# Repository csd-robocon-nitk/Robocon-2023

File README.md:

# Overview
This repository contains all the codes and PCB designs used for ABU Robocon 2023.

# Technolgies Used

# Directory Structure

- ```Experimental``` Contains all the arduino codes used during the ideation and prototyping phase. The folder also contains python codes used for image processing using Kinect cameras.

- ```Final Codes``` Contains all the arduino codes used in the competition.

- ```PCB``` Designs of the PCBs used in the robots is present here.

- ```Media``` Folder for keeping images for documentation.

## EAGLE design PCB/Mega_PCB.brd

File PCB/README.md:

# PCB designs for the Mega and Nano PCB for Robocon 2023

The elephant and the rabbit robot each uses two PCBs. The PCBs have been designed in Autodesk Eagle.

## Mega PCB

*Mega PCB*

The first PCB contains the Arduino Mega (Also compatible with Arduino Giga, and Arduino Due). This PCB is connected to all the motors responsible for the navigation of the robots and IMU module. The PCB also has pin headers for ESP-07 for WiFi communication.

## Nano PCB

*Nano PCB*

The second PCB contains the Arduino Nano (Also compatible with boards of same form factor as Arduino Nano). This PCB controls the rest of the robot, which includes the shooting and picking mechanism. 

The boards have been designed such that they can be used together or as seperate standalone modules.

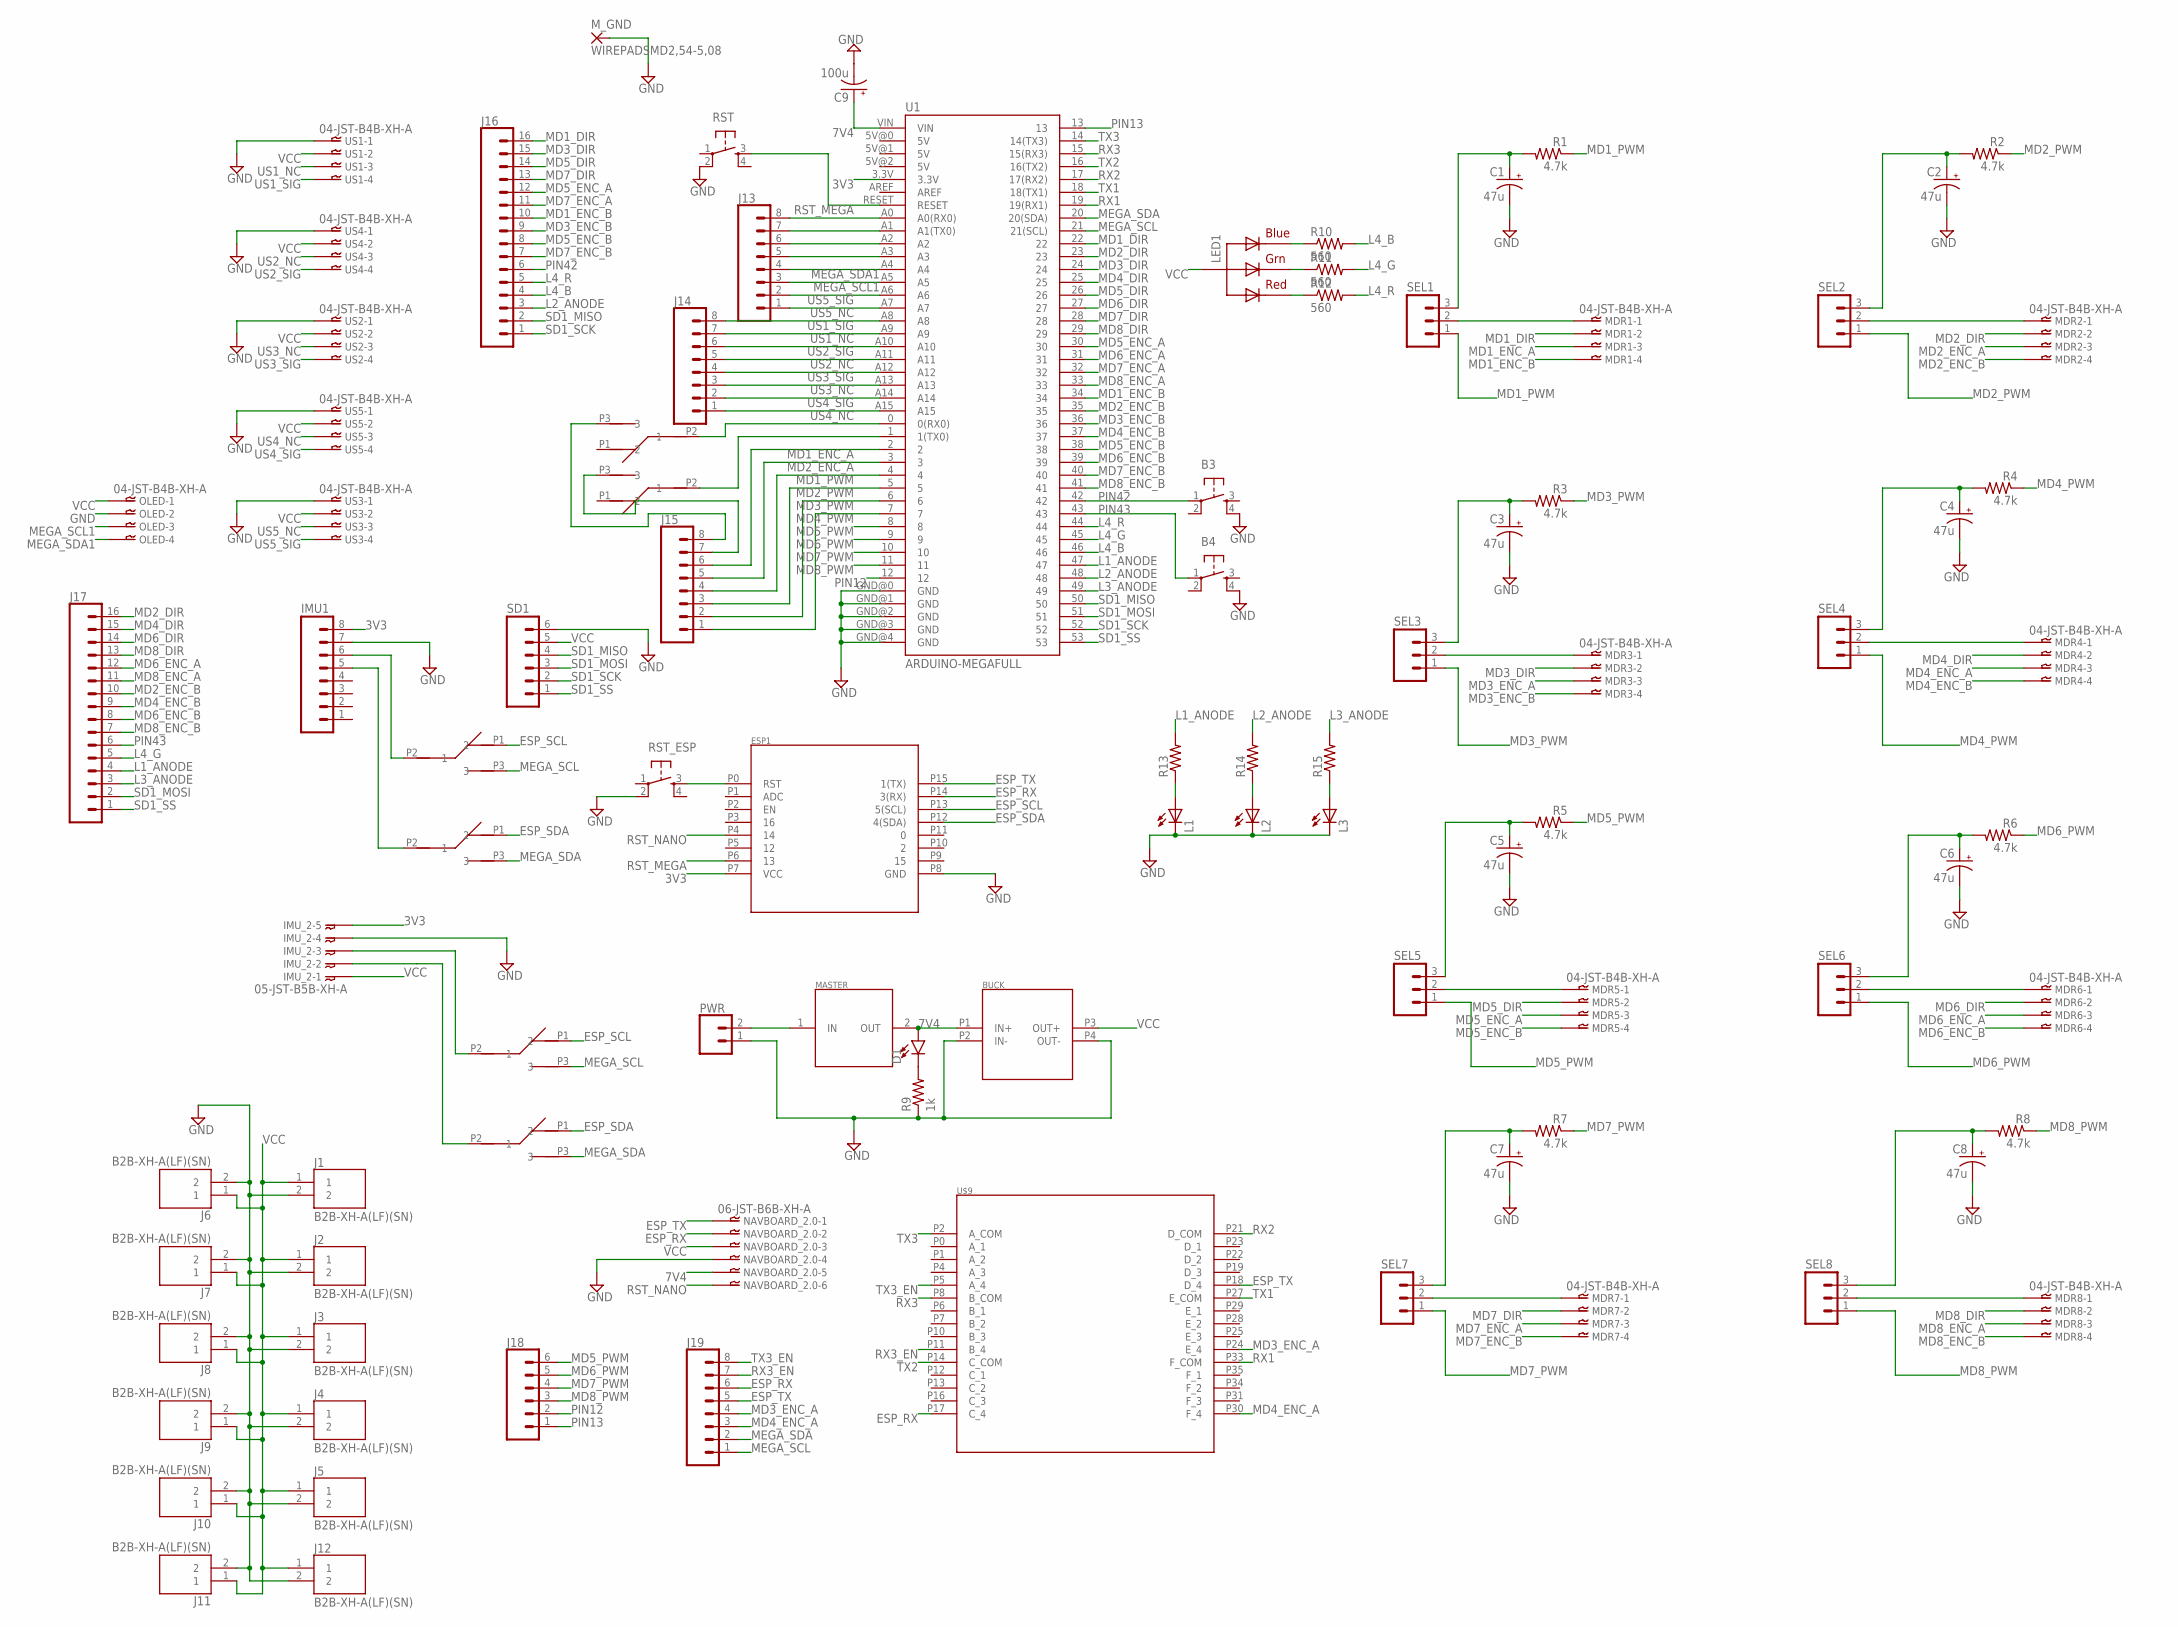
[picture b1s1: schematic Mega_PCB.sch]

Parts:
B3, B4: TAC_SWITCHPTH; TACTILE-PTH
BUCK: 5V_BUCK
C1, C2, C3, C4, C5, C6, C7, C8: 47u; E2-5
C9: 100u; TT2D6
D1: LED5MM; LED_5MM
ESP1: ESP07
IMU1: M081X08; 1X08
IMU1_SCL_SEL, IMU1_SDA_SEL, IMU2_SCL_SEL, IMU2_SDA_SEL: SLIDE_SWITCH
IMU_2: 05-JST-B5B-XH-A; B5B-XH
J1, J2, J3, J4, J5, J6, J7, J8, J9, J10, J11, J12: B2B-XH-A(LF)(SN); JST_B2B-XH-A(LF)(SN)
J13, J14, J15, J19: CONN_08"; 1X08
J16, J17: CONN_16; 1X16
J18: CONN_06SILK_FEMALE_PTH; 1X06
L1, L2, L3: LED3MM
LED1: RGBLED_CA-5MM; LED5MMRGB
MASTER: MED_SWITCH
MDR1, MDR2, MDR3, MDR4, MDR5, MDR6, MDR7, MDR8: 04-JST-B4B-XH-A; B4B-XH
M_GND: WIREPADSMD2,54-5,08; SMD2,54-5,08
NAVBOARD_2.0: 06-JST-B6B-XH-A; B6B-XH
OLED: 04-JST-B4B-XH-A; B4B-XH
PWR: CONN_02PTH4; 1X02_XTRA_BIG
R1, R2, R3, R4, R5, R6, R7, R8: 4.7k; 0204/7
R9: 1k; 0204/7
R10, R11, R12: 560; 0204/7
R13, R14, R15: R-US_0204/7; 0204/7
RST: TAC_SWITCHPTH; TACTILE-PTH
RST_ESP: TAC_SWITCHPTH; TACTILE-PTH
SD1: M06SIP; 1X06
SEL1, SEL2, SEL3, SEL4, SEL5, SEL6, SEL7, SEL8: M03PTH; 1X03
U1: ARDUINO-MEGAFULL; ARDUINO_MEGA
U$3, U$4: SLIDE_SWITCH
U$9: CATERPILLAR
US1, US2, US3, US4, US5: 04-JST-B4B-XH-A; B4B-XH

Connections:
3V3: ESP1.P7 (VCC), IMU1.8, IMU_2.P$5, U1.3.3V
7V4: BUCK.P1 (IN+), C9.+, D1.A, MASTER.2 (OUT), NAVBOARD_2.0.P$5, U1.VIN
ESP_RX: ESP1.P14 (3(RX)), J19.6, NAVBOARD_2.0.P$2, U$9.P17 (C_4)
ESP_SCL: ESP1.P13 (5(SCL)), IMU1_SCL_SEL.P1 (2), IMU2_SCL_SEL.P1 (2)
ESP_SDA: ESP1.P12 (4(SDA)), IMU1_SDA_SEL.P1 (2), IMU2_SDA_SEL.P1 (2)
ESP_TX: ESP1.P15 (1(TX)), J19.5, NAVBOARD_2.0.P$1, U$9.P18 (D_4)
GND: B3.4, B4.4, BUCK.P2 (IN-), BUCK.P4 (OUT-), C1.-, C2.-, C3.-, C4.-, C5.-, C6.-, C7.-, C8.-, C9.-, ESP1.P8 (GND), IMU1.7, IMU_2.P$4, J1.2, J2.2, J3.2, J4.2, J5.2, J6.2, J7.2, J8.2, J9.2, J10.2, J11.2, J12.2, L1.K (C), L2.K (C), L3.K (C), M_GND.1, NAVBOARD_2.0.P$4, OLED.P$2, PWR.1, R9.1, RST.2, RST_ESP.2, SD1.6, U1.GND@0 (GND), U1.GND@1 (GND), U1.GND@2 (GND), U1.GND@3 (GND), U1.GND@4 (GND), US1.P$1, US2.P$1, US3.P$1, US4.P$1, US5.P$1
IMU_SDA: IMU1.5, IMU1_SDA_SEL.P2 (1)
IMU_SDA1: IMU2_SDA_SEL.P2 (1), IMU_2.P$2
L1_ANODE: J17.4, R13.2, U1.47
L2_ANODE: J16.3, R14.2, U1.48
L3_ANODE: J17.3, R15.2, U1.49
L4_B: J16.4, R10.2, U1.46
L4_G: J17.5, R11.2, U1.45
L4_R: J16.5, R12.2, U1.44
MD1_DIR: J16.16, MDR1.P$2, U1.22
MD1_ENC_A: J15.6, MDR1.P$3, U1.2
MD1_ENC_B: J16.10, MDR1.P$4, U1.34
MD1_PWM: J15.4, R1.1, SEL1.1, U1.4
MD2_DIR: J17.16, MDR2.P$2, U1.23
MD2_ENC_A: J15.5, MDR2.P$3, U1.3
MD2_ENC_B: J17.10, MDR2.P$4, U1.35
MD2_PWM: J15.3, R2.1, SEL2.1, U1.5
MD3_DIR: J16.15, MDR3.P$2, U1.24
MD3_ENC_A: J19.4, MDR3.P$3, U$9.P24 (E_4)
MD3_ENC_B: J16.9, MDR3.P$4, U1.36
MD3_PWM: J15.2, R3.1, SEL3.1, U1.6
MD4_DIR: J17.15, MDR4.P$2, U1.25
MD4_ENC_A: J19.3, MDR4.P$3, U$9.P30 (F_4)
MD4_ENC_B: J17.9, MDR4.P$4, U1.37
MD4_PWM: J15.1, R4.1, SEL4.1, U1.7
MD5_DIR: J16.14, MDR5.P$2, U1.26
MD5_ENC_A: J16.12, MDR5.P$3, U1.30
MD5_ENC_B: J16.8, MDR5.P$4, U1.38
MD5_PWM: J18.6, R5.1, SEL5.1, U1.8
MD6_DIR: J17.14, MDR6.P$2, U1.27
MD6_ENC_A: J17.12, MDR6.P$3, U1.31
MD6_ENC_B: J17.8, MDR6.P$4, U1.39
MD6_PWM: J18.5, R6.1, SEL6.1, U1.9
MD7_DIR: J16.13, MDR7.P$2, U1.28
MD7_ENC_A: J16.11, MDR7.P$3, U1.32
MD7_ENC_B: J16.7, MDR7.P$4, U1.40
MD7_PWM: J18.4, R7.1, SEL7.1, U1.10
MD8_DIR: J17.13, MDR8.P$2, U1.29
MD8_ENC_A: J17.11, MDR8.P$3, U1.33
MD8_ENC_B: J17.7, MDR8.P$4, U1.41
MD8_PWM: J18.3, R8.1, SEL8.1, U1.11
MEGA_SCL: IMU1_SCL_SEL.P3 (3), IMU2_SCL_SEL.P3 (3), J19.1, U1.21 (21(SCL))
MEGA_SCL1: J13.3, OLED.P$3, U1.A5
MEGA_SDA: IMU1_SDA_SEL.P3 (3), IMU2_SDA_SEL.P3 (3), J19.2, U1.20 (20(SDA))
MEGA_SDA1: J13.4, OLED.P$4, U1.A4
unnamed: MDR2.P$1, SEL2.2
unnamed: C2.+, R2.2, SEL2.3
unnamed: MDR3.P$1, SEL3.2
unnamed: MDR1.P$1, SEL1.2
unnamed: C3.+, R3.2, SEL3.3
unnamed: C4.+, R4.2, SEL4.3
unnamed: C8.+, R8.2, SEL8.3
unnamed: C6.+, R6.2, SEL6.3
unnamed: MDR4.P$1, SEL4.2
unnamed: MDR8.P$1, SEL8.2
unnamed: C5.+, R5.2, SEL5.3
unnamed: IMU1.6, IMU1_SCL_SEL.P2 (1)
unnamed: D1.K (C), R9.2
unnamed: LED1.4 (BLUE), R10.1
unnamed: J13.8, U1.A0 (A0(RX0))
unnamed: C1.+, R1.2, SEL1.3
unnamed: MDR5.P$1, SEL5.2
unnamed: MDR6.P$1, SEL6.2
unnamed: U1.0 (0(RX0)), U$3.P2 (1)
unnamed: U1.1 (1(TX0)), U$4.P2 (1)
unnamed: IMU2_SCL_SEL.P2 (1), IMU_2.P$3
unnamed: C7.+, R7.2, SEL7.3
unnamed: MDR7.P$1, SEL7.2
unnamed: J13.7, U1.A1 (A1(TX0))
unnamed: ESP1.P0 (RST), RST_ESP.3
unnamed: J13.6, U1.A2
unnamed: J13.5, U1.A3
unnamed: J15.8, U$3.P3 (3)
unnamed: J15.7, U$4.P3 (3)
unnamed: LED1.3 (GREEN), R11.1
unnamed: LED1.1 (RED), R12.1
unnamed: L1.A, R13.1
unnamed: L2.A, R14.1
unnamed: L3.A, R15.1
N&N: MASTER.1 (IN), PWR.2
PIN12: J18.2, U1.12
PIN13: J18.1, U1.13
PIN42: B3.1, J16.6, U1.42
PIN43: B4.1, J17.6, U1.43
RST_MEGA: ESP1.P6 (13), RST.3, U1.RESET
RST_NANO: ESP1.P4 (14), NAVBOARD_2.0.P$6
RX1: U1.19 (19(RX1)), U$9.P33 (F_COM)
RX2: U1.17 (17(RX2)), U$9.P21 (D_COM)
RX3: U1.15 (15(RX3)), U$9.P8 (B_COM)
RX3_EN: J19.7, U$9.P11 (B_4)
SD1_MISO: J16.2, SD1.4, U1.50
SD1_MOSI: J17.2, SD1.3, U1.51
SD1_SCK: J16.1, SD1.2, U1.52
SD1_SS: J17.1, SD1.1, U1.53
TX1: U1.18 (18(TX1)), U$9.P27 (E_COM)
TX2: U1.16 (16(TX2)), U$9.P14 (C_COM)
TX3: U1.14 (14(TX3)), U$9.P2 (A_COM)
TX3_EN: J19.8, U$9.P5 (A_4)
US1_NC: J14.7, U1.A9, US1.P$3
US1_SIG: J14.8, U1.A8, US1.P$4
US2_NC: J14.5, U1.A11, US4.P$3
US2_SIG: J14.6, U1.A10, US4.P$4
US3_NC: J14.3, U1.A13, US2.P$3
US3_SIG: J14.4, U1.A12, US2.P$4
US4_NC: J14.1, U1.A15, US5.P$3
US4_SIG: J14.2, U1.A14, US5.P$4
US5_NC: J13.1, U1.A7, US3.P$3
US5_SIG: J13.2, U1.A6, US3.P$4
VCC: BUCK.P3 (OUT+), IMU_2.P$1, J1.1, J2.1, J3.1, J4.1, J5.1, J6.1, J7.1, J8.1, J9.1, J10.1, J11.1, J12.1, LED1.2 (VCC), NAVBOARD_2.0.P$3, OLED.P$1, SD1.5, US1.P$2, US2.P$2, US3.P$2, US4.P$2, US5.P$2

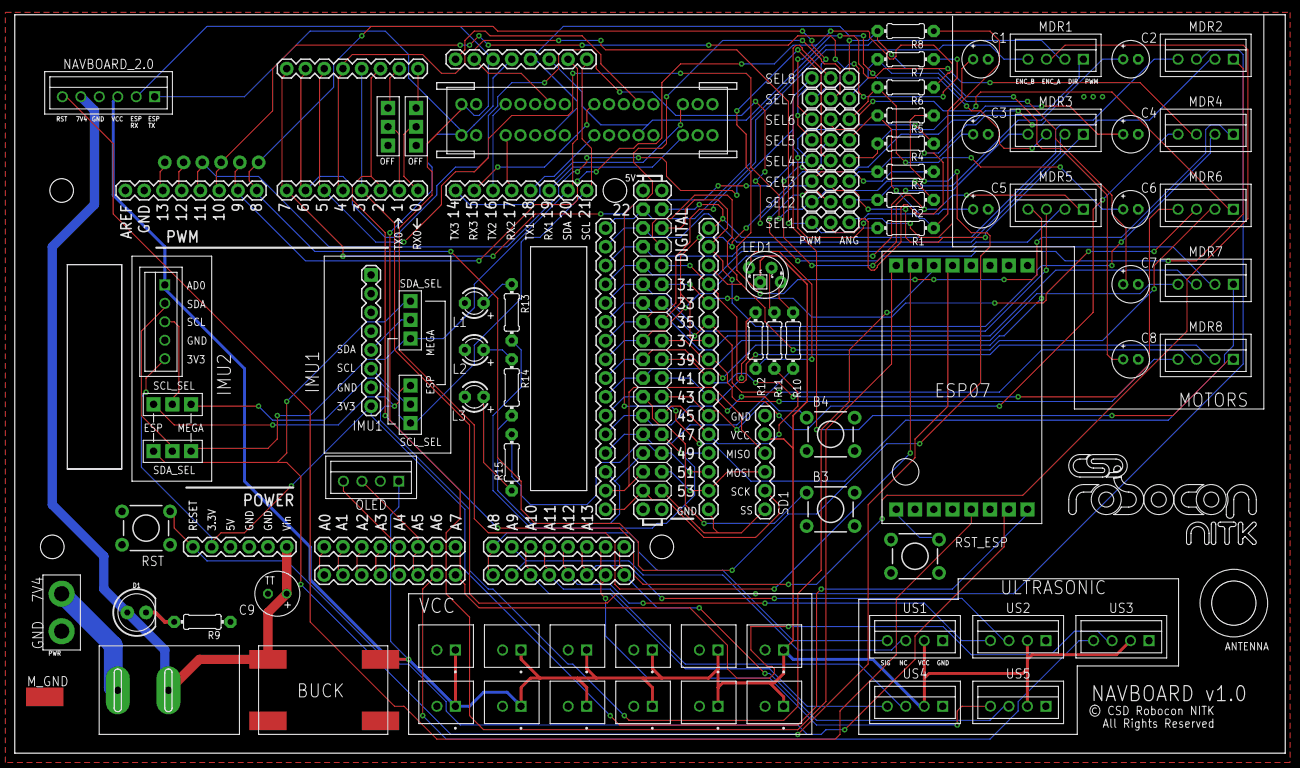
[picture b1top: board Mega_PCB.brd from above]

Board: 2 copper layers, 171.9 x 99.9 mm, 92 parts (1 on the bottom side), 115 nets.

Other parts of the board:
U$1: LOGO

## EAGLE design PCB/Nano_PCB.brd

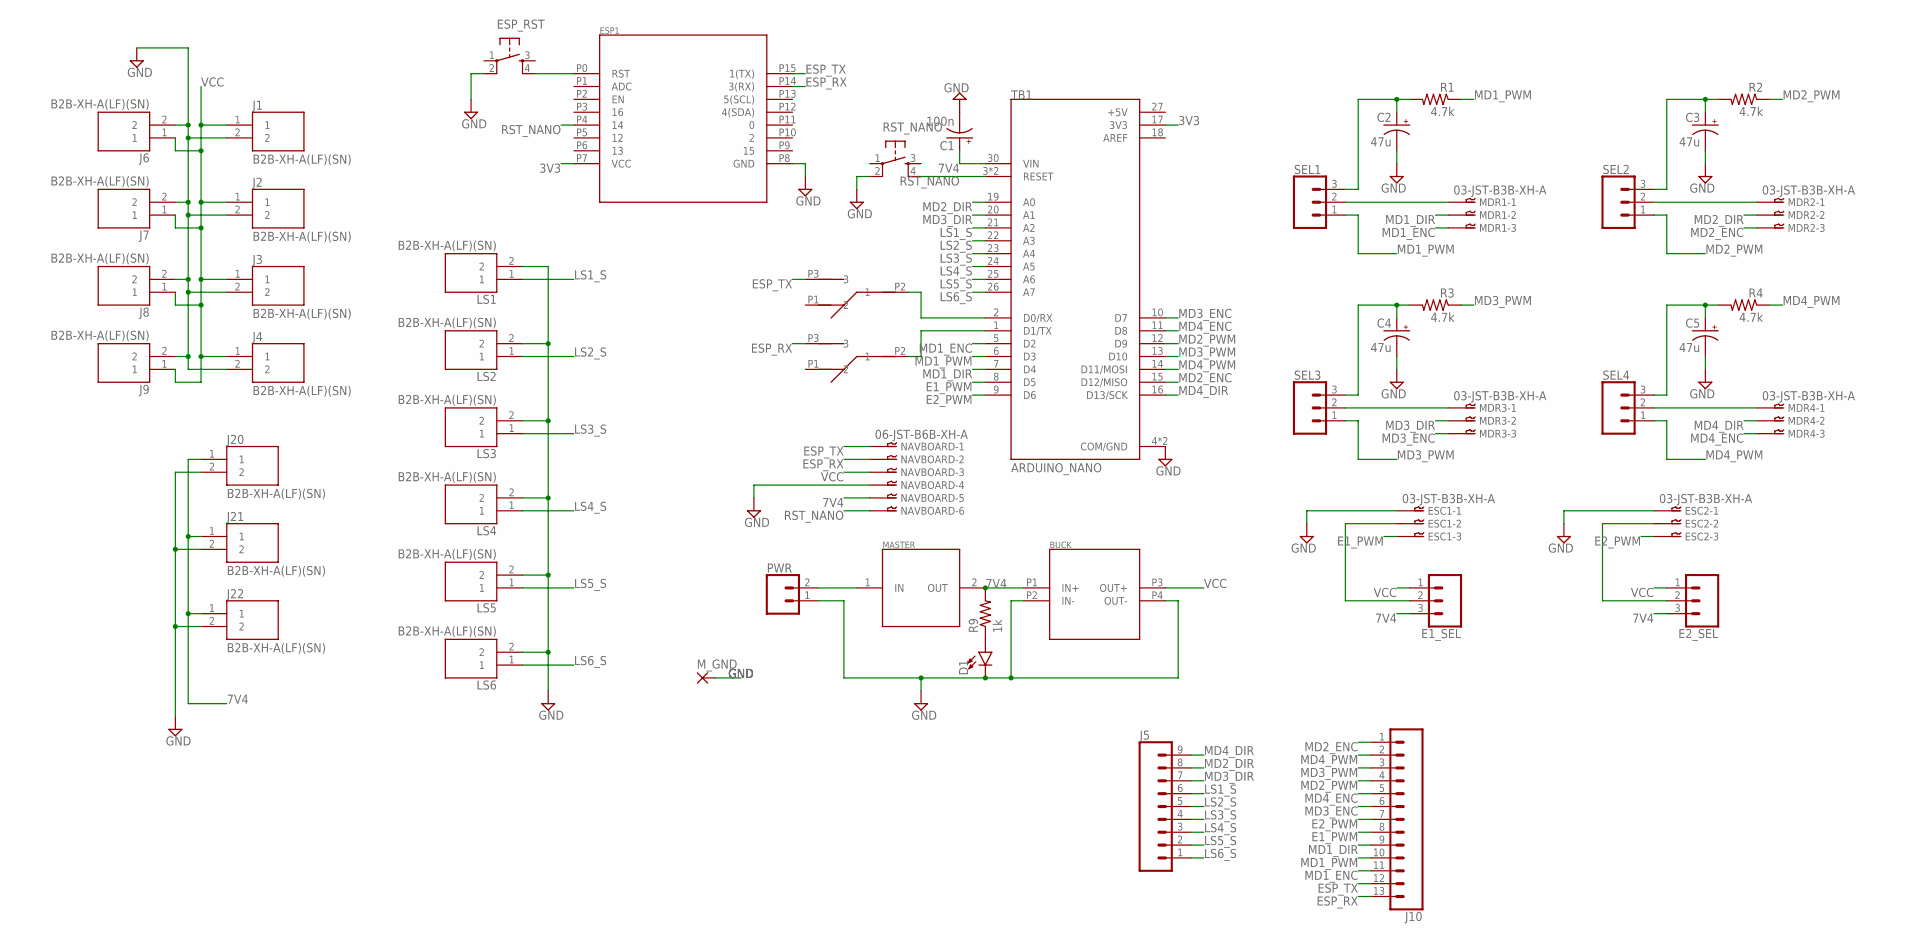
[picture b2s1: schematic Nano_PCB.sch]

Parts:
BUCK: 5V_BUCK
C1: 100n; TT2D6
C2, C3, C4, C5: 47u; E2-5
D1: LED3MM; LED_3MM
E1_SEL, E2_SEL: CONN_03; 1X03
ESC1, ESC2: 03-JST-B3B-XH-A; B3B-XH
ESP1: ESP07
ESP_RST: TAC_SWITCHPTH; TACTILE-PTH
J1, J2, J3, J4, J6, J7, J8, J9, J20, J21, J22: B2B-XH-A(LF)(SN); JST_B2B-XH-A(LF)(SN)
J5: CONN_09; 1X09
J10: CONN_13; 1X13
LS1, LS2, LS3, LS4, LS5, LS6: B2B-XH-A(LF)(SN); JST_B2B-XH-A(LF)(SN)
MASTER: MED_SWITCH
MDR1, MDR2, MDR3, MDR4: 03-JST-B3B-XH-A; B3B-XH
M_GND: WIREPADSMD5-2,5; 5-2,5
NAVBOARD: 06-JST-B6B-XH-A; B6B-XH
PWR: CONN_02PTH4; 1X02_XTRA_BIG
R1, R2, R3, R4: 4.7k; 0204/7
R9: 1k; 0204/7
RST_NANO: TAC_SWITCHPTH; TACTILE-PTH
SEL1, SEL2, SEL3, SEL4: CONN_03; 1X03
TB1: ARDUINO_NANO; SHIELD_ARDUINO_NANO
U$1, U$2: SLIDE_SWITCH

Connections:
3V3: ESP1.P7 (VCC), TB1.17 (3V3)
7V4: BUCK.P1 (IN+), C1.+, E1_SEL.3, E2_SEL.3, J20.1, J21.1, J22.1, MASTER.2 (OUT), NAVBOARD.P$5, R9.2, TB1.30 (VIN)
+5V: TB1.27 (+5V)
AREF: TB1.18 (AREF)
E1_PWM: ESC1.P$3, J10.8, TB1.8 (D5)
E2_PWM: ESC2.P$3, J10.7, TB1.9 (D6)
ESP_RX: ESP1.P14 (3(RX)), J10.13, NAVBOARD.P$2, U$2.P3 (3)
ESP_TX: ESP1.P15 (1(TX)), J10.12, NAVBOARD.P$1, U$1.P3 (3)
GND: BUCK.P2 (IN-), BUCK.P4 (OUT-), C1.-, C2.-, C3.-, C4.-, C5.-, D1.K (C), ESC1.P$1, ESC2.P$1, ESP1.P8 (GND), ESP_RST.2, J1.2, J2.2, J3.2, J4.2, J6.2, J7.2, J8.2, J9.2, J20.2, J21.2, J22.2, LS1.2, LS2.2, LS3.2, LS4.2, LS5.2, LS6.2, M_GND.1, NAVBOARD.P$4, PWR.1, RST_NANO.2, TB1.4 (COM/GND), TB1.29 (COM/GND)
LS1_S: J5.6, LS1.1, TB1.21 (A2)
LS2_S: J5.5, LS2.1, TB1.22 (A3)
LS3_S: J5.4, LS3.1, TB1.23 (A4)
LS4_S: J5.3, LS4.1, TB1.24 (A5)
LS5_S: J5.2, LS5.1, TB1.25 (A6)
LS6_S: J5.1, LS6.1, TB1.26 (A7)
MD1_DIR: J10.9, MDR1.P$2, TB1.7 (D4)
MD1_ENC: J10.11, MDR1.P$3, TB1.5 (D2)
MD1_PWM: J10.10, R1.1, SEL1.1, TB1.6 (D3)
MD2_DIR: J5.8, MDR2.P$2, TB1.19 (A0)
MD2_ENC: J10.1, MDR2.P$3, TB1.15 (D12/MISO)
MD2_PWM: J10.4, R2.1, SEL2.1, TB1.12 (D9)
MD3_DIR: J5.7, MDR3.P$2, TB1.20 (A1)
MD3_ENC: J10.6, MDR3.P$3, TB1.10 (D7)
MD3_PWM: J10.3, R3.1, SEL3.1, TB1.13 (D10)
MD4_DIR: J5.9, MDR4.P$2, TB1.16 (D13/SCK)
MD4_ENC: J10.5, MDR4.P$3, TB1.11 (D8)
MD4_PWM: J10.2, R4.1, SEL4.1, TB1.14 (D11/MOSI)
unnamed: TB1.2 (D0/RX), U$1.P2 (1)
unnamed: C3.+, R2.2, SEL2.3
unnamed: TB1.1 (D1/TX), U$2.P2 (1)
unnamed: MDR2.P$1, SEL2.2
unnamed: MDR1.P$1, SEL1.2
unnamed: C4.+, R3.2, SEL3.3
unnamed: MDR3.P$1, SEL3.2
unnamed: C5.+, R4.2, SEL4.3
unnamed: MDR4.P$1, SEL4.2
unnamed: E2_SEL.2, ESC2.P$2
unnamed: E1_SEL.2, ESC1.P$2
unnamed: D1.A, R9.1
unnamed: ESP1.P0 (RST), ESP_RST.4
unnamed: C2.+, R1.2, SEL1.3
N&N: MASTER.1 (IN), PWR.2
RST_NANO: ESP1.P4 (14), NAVBOARD.P$6, RST_NANO.4, TB1.3 (RESET), TB1.28 (RESET)
VCC: BUCK.P3 (OUT+), E1_SEL.1, E2_SEL.1, J1.1, J2.1, J3.1, J4.1, J6.1, J7.1, J8.1, J9.1, NAVBOARD.P$3

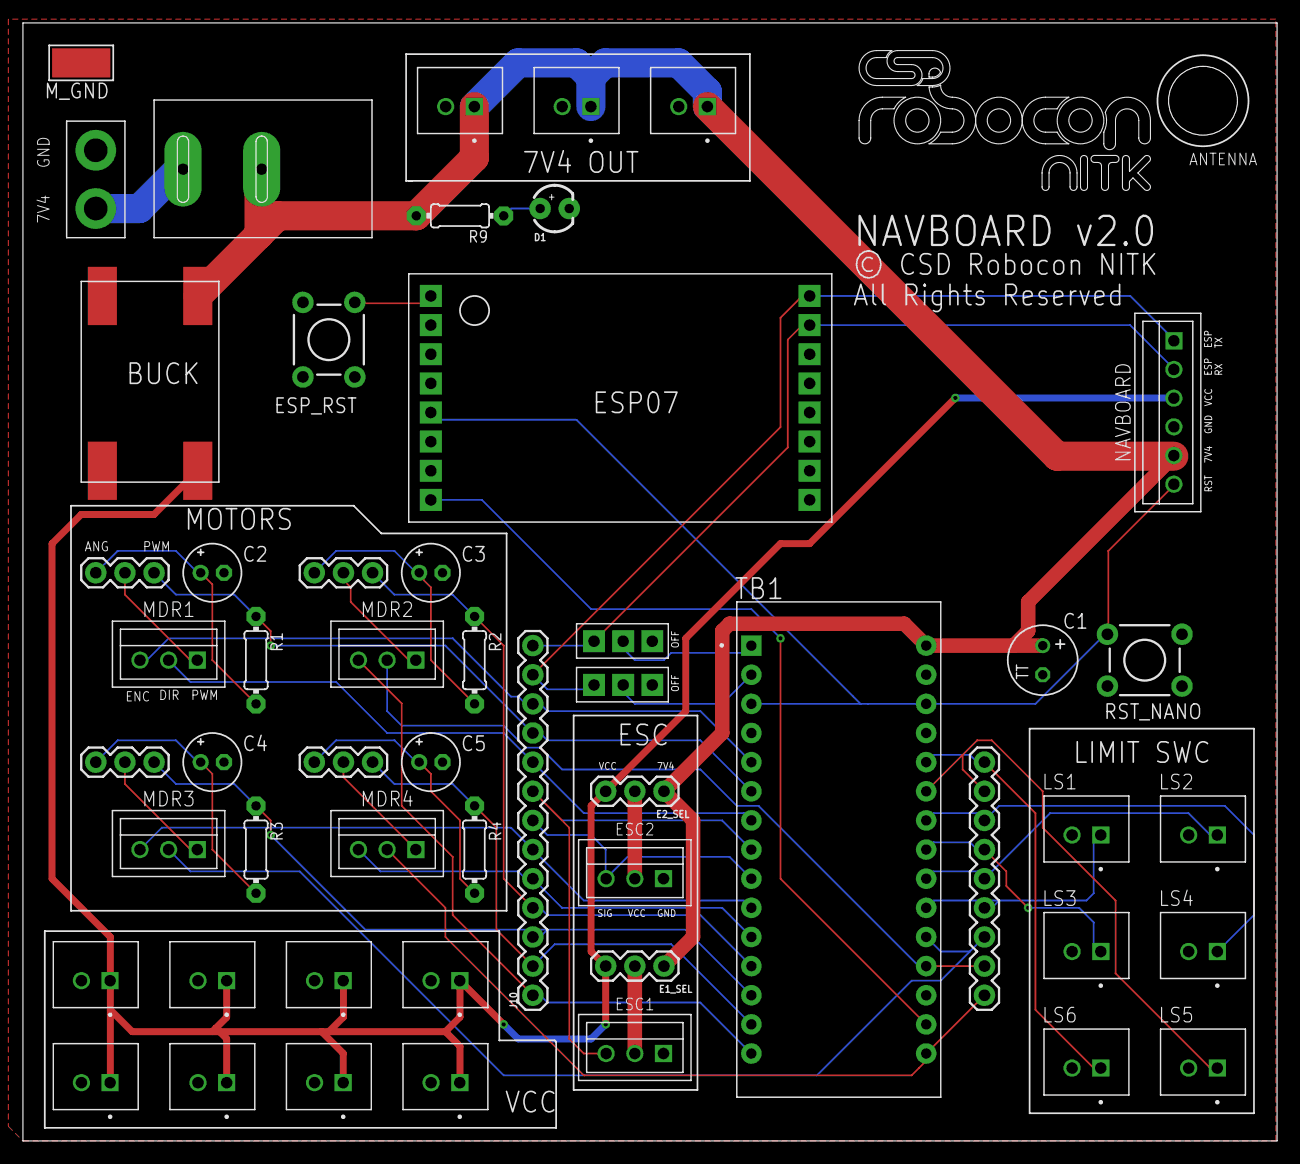
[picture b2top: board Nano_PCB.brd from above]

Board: 2 copper layers, 109.3 x 97.5 mm, 54 parts (0 on the bottom side), 42 nets.

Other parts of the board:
U$5: LOGO

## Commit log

2022-11-04 Kinect packages Installation readme
2022-11-17 Arduino Codes Updated
2022-11-17 Codes Updated
2022-11-18 Holonomic Updated
2022-11-19 adding kinect code
2022-11-19 moving files
2022-11-19 Wirless Communication Codes
2022-11-23 Minor Bugs fixed
2022-11-26 Motor Encoder test code and position code updated
2022-12-04 MPU6050 Angle Measurement
2022-12-06 Speed control implemented
2022-12-08 Wireless_Com Done
2022-12-19 Added installation instructions
2023-01-03 Codes for PI Controller Updated
2023-01-14 Code for angle Control Updated
2023-01-17 Codes for 4 Wheeled OmniBot
2023-01-17 Codes for three wheeled OmniBot
2023-01-18 Added Mocemcu Reciever Code
2023-02-23 Added code for BLDC Motor Testing
2023-02-23 Uodated README
2023-03-04 Wall Follow Check
2023-03-04 Tilt Mech Updated
2023-03-14 Final Bot Code Updated
2023-03-19 Codes for WiFi Updated
2023-03-19 Relative Frame Navigation for ER Updated
2023-03-19 RR Navigation Updated
2023-03-20 Global Frame Navigation Updated
2023-03-23 Added remote reset and manual picking features
2023-03-23 Code for MPU9250
2023-03-23 Angle from MPU using Timers
2023-03-23 Fixed Typo
2023-03-23 Updated code for Global Frame Nav
2023-03-28 MPU for ESP07
2023-03-31 Modified ER code and esp-07 code
2023-03-31 MPU and wallfollow
2023-04-01 fixed esp 07 code
2023-04-01 ER Code Updated
2023-04-01 Fixed minor errors
2023-04-01 RR Navigation Code Updated
2023-04-02 RR yet to tune
2023-04-04 Added MPU Reset Code
2023-04-04 Updated Wall Following Code
2023-04-05 Added symbols for Pick, Shoot, Tilt, Power and Reload
2023-04-05 Manual control code updated
2023-04-05 Added Nodemcu manual code for er
2023-04-06 Manual Code Updated for ER
2023-04-08 Updated Manual Control for ER and RR
2023-04-09 Reset Code Updated
2023-04-09 Updated some RR stuff
2023-04-09 Push Servo Code Updated
2023-04-09 BLDC Speed control
2023-04-09 Updated RR Manual Code
2023-04-10 BLDC integrated with RR bot code
2023-04-10 Fixed infinite reload bug in ER
2023-04-11 Some changes
2023-04-12 Small Fixes
2023-04-12 Added global nav
2023-04-13 RR Code Updated
2023-04-13 BLDC code for amanual bot updated
2023-04-25 Added ER Nano Code
2023-05-04 Tuned PI Controller
2023-05-04 Added Corner Adjustment Code
2023-05-11 MPU with actuator testing code
2023-05-11 Updated Direct Communication Code
2023-05-19 Added code for RR Manual with PI Tuned
2023-05-23 Removed other functionalities except navigation
2023-05-23 Adding template for final code for the robots
2023-05-23 Wifi Communication setup
2023-05-23 Manual Navigation for ER and RR Updated
2023-05-25 Added reload sequence template
2023-05-25 Template nano code for ER complete
2023-05-26 Partially completed ER code
2023-05-26 Fixed Syntax Error
2023-05-26 Updated RR side navigation and controller code
2023-05-29 Manual nano side code done
2023-05-29 Manunal controls code template done
2023-05-29 Final code template for controller side nano done
2023-05-29 PI controller tuned
2023-05-29 Updated controller code
2023-05-30 RR Speed Up
2023-05-30 Updated shoot sequence to run on startup
2023-05-30 Added template code for rr side nano
2023-06-01 RR Side Nano code updated
2023-06-03 pin numbers updated
2023-06-10 Web socket code for controller
2023-06-19 Added reconnection code
2023-06-19 Updated code to work with NodeMCU based controller
2023-06-19 Added PCB designs
2023-06-19 Organised all files
2023-06-19 Organised files
2023-06-19 Organised shooting mechanism codes
2023-06-30 Added comments for codes
2023-06-30 Codes for Kinect added
2023-06-30 Added comments
2023-06-30 Updated logo
2023-07-04 Update README for PCB
2023-07-04 Added comments for final set of codes

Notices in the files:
PCB/Mega_PCB.brd:
© CSD Robocon NITK
All Rights Reserved
parts and their libraries:
SparkFun: Licensing: CC v3.0 Share-Alike You are welcome to use this library for commercial purposes.
SparkFun-Connectors: Licensing: Creative Commons ShareAlike 4.0 International - https://creativecommons.org/licenses/by-sa/4.0
